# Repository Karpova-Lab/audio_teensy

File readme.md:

# Teensy Audio Board for pyControl

This device connects with a [pyControl breakout](https://karpova-lab.github.io/pyControl-D-Series-Breakout/index.html) to play audio tones. 
A [Teensy 3.2](https://www.pjrc.com/teensy/index.html) generates an i2s audio signal which is later decompressed and amplified by the SGTL5000 codec IC. 
A left and right amplified signal is output to two separate mono headphone jacks. The design of this pcb is based on the [Teensy Audio Adaptor Board](https://www.pjrc.com/store/teensy3_audio.html).

## Bill Of Materials
| Qty | Reference  | Description         | Value/MPN                                                                                                            | 
|-----|------------|---------------------|----------------------------------------------------------------------------------------------------------------------|
| 3   | C2, C3, C7 | 0603 Capacitor      | [100nF](https://www.digikey.com/products/en?keywords=1276-1258-1-ND)                                                 | 
| 1   | C4         | 0603 Capacitor      | [150nF](https://www.digikey.com/product-detail/en/kemet/C0603C154K8RACTU/399-7862-1-ND/3471585)                      | 
| 2   | C5, C1     | 0603 Capacitor      | [1.0µF](https://www.digikey.com/products/en?keywords=1276-6524-1-ND)                                                 | 
| 1   | C6         | 0603 Capacitor      | [2.2µF](https://www.digikey.com/products/en?keywords=1276-1040-1-ND)                                                 | 
| 1   | FB1        | 0603 Ferrite Bead   | [600Ω @ 100MHz](https://www.digikey.com/products/en?keywords=445-2166-1-ND)                                          | 
| 1   | J1         | RJ45 Jack           | [54602-908LF](https://www.digikey.com/en/products/detail/54602-908LF/609-1046-ND/1001360)                            | 
| 2   | J3, J2     | 14pin Female Header | [SSM-114-L-SV-BE](https://www.digikey.com/products/en?keywords=SSM-114-L-SV-BE-ND)                                   | 
| 2   | J4, J5     | Mono Audio Jack     | [4832.2230](https://www.digikey.com/en/products/detail/schurter-inc/4832-2230/1731054?s=N4IgTCBcDaICwA4BsBaAzHAjAdhAXQF8g)| 
| 1   | R1         | 0603 Resistor       | [100Ω](https://www.digikey.com/products/en?keywords=311-100HRCT-ND)                                                  | 
| 2   | R3, R2     | 0603 Resistor       | [2.2KΩ](https://www.digikey.com/products/en?keywords=A130093CT-ND)                                                   | 
| 1   | U2         | 1.8V LDO Regulator  | [AP7313](https://www.digikey.com/product-detail/en/diodes-incorporated/AP7313-18SAG-7/AP7313-18SAG-7DICT-ND/2270838) | 
| 1   | U3         | Codec IC            | [SGTL5000](https://www.digikey.com/products/en?keywords=SGTL5000XNAA3R2CT-ND)                                        | 

### [View interactive BOM](https://karpova-lab.github.io/audio_teensy/ibom)

## Example Firmware for Teensy
This following firmware creates 6.5KHz and 14KHz sine waves that are frequency modulated at 6.66 Hz. 
It responds to commands received over serial UART. 'L' plays the left tone, 'R' plays the right tone, 'S' stops playing both tones, 'V,5' adjust the volume to 5. 
This firmware is loaded onto the Teensy microcontroller. 

[Audio System Design Tool](https://www.pjrc.com/teensy/gui/index.html)

```c++
#include <Audio.h>
#include <Wire.h>
#include <SPI.h>
#include <SD.h>
#include <SerialFlash.h>

// GUItool: begin automatically generated code
AudioSynthWaveformSine   modulation;     //xy=323.0056381225586,328.0056438446045
AudioSynthWaveformModulated left_tone;   //xy=530.0056648254395,308.0056457519531
AudioSynthWaveformModulated right_tone;   //xy=533.1874694824219,363.0965919494629
AudioMixer4              mixer;         //xy=719.1874771118164,330.0965805053711
AudioOutputI2S           i2s;            //xy=868.0056648254395,332.0056505203247
AudioConnection          patchCord1(modulation, 0, left_tone, 0);
AudioConnection          patchCord2(modulation, 0, right_tone, 0);
AudioConnection          patchCord3(left_tone, 0, mixer, 0);
AudioConnection          patchCord4(right_tone, 0, mixer, 1);
AudioConnection          patchCord5(mixer, 0, i2s, 0);
AudioConnection          patchCord6(mixer, 0, i2s, 1);
AudioControlSGTL5000     codec;          //xy=607.0056762695312,492.0056781768799
// GUItool: end automatically generated code

int current_waveform=0;
const int LED = 13;

void setup() {
  // put your setup code here, to run once:
  AudioMemory(10);
  codec.enable();
  codec.volume(0.10);

  modulation.frequency(20/3.0);
  modulation.amplitude(.019);

  left_tone.frequency(6500);
  left_tone.amplitude(1.0);
  right_tone.frequency(14000);
  right_tone.amplitude(1.0);

  mixer.gain(0,0);
  mixer.gain(1,0);

  current_waveform = WAVEFORM_SINE;
  left_tone.begin(current_waveform);
  right_tone.begin(current_waveform);
  Serial1.begin(9600);
  pinMode(LED,OUTPUT);
  digitalWrite(LED,LOW);
 }

void loop() {
  if (Serial1.available()){
    char msg = Serial1.read();
    if (msg=='L' | msg == 'R' | msg == 'S' | msg == 'V'){
      if (msg=='L'){ // left tone
        mixer.gain(0,1);
        mixer.gain(1,0);
        digitalWrite(LED,HIGH);
      }
      else if (msg=='R'){ //right tone
        mixer.gain(0,0);
        mixer.gain(1,1);
        digitalWrite(LED,HIGH);
      }
      else if (msg=='S'){ 
        mixer.gain(0,0);
        mixer.gain(1,0);
        digitalWrite(LED,LOW);
      }
      else if (msg=='V'){ 
        float volume = parseData();
        volume = 2*volume/100.0;
        codec.volume(volume);
      }
    }    
  }
}

int parseData(){
  char msgData[10] = "";
  Serial1.readBytesUntil('\n',msgData,10);
  char* msgPointer;
  msgPointer = strtok(msgData,",");
  return atoi(msgPointer);
}
```

## pyControl Device file

``` python
from machine import UART
from array import array

class Teensy_audio():
    def __init__(self, port):
        assert port.UART is not None, '! Teensy Audio Player needs a port with UART.'
        self.uart = UART(port.UART, 9600)
        self.uart.init(9600, bits=8, parity=None, stop=1, timeout=1)
        self.uart.write('S')

    def play(self, side):
        if side == 'Left':
            self.uart.write('L')
        elif side == 'Right':
            self.uart.write('R')
        return True

    def stop(self):
        self.uart.write('S')
        return False

    def set_volume(self, volume): # Between 1 - 65
        self.uart.write('V,{}'.format(volume))
```

## Latency
The start and stop latencies are both about 6.5 ± 1 ms

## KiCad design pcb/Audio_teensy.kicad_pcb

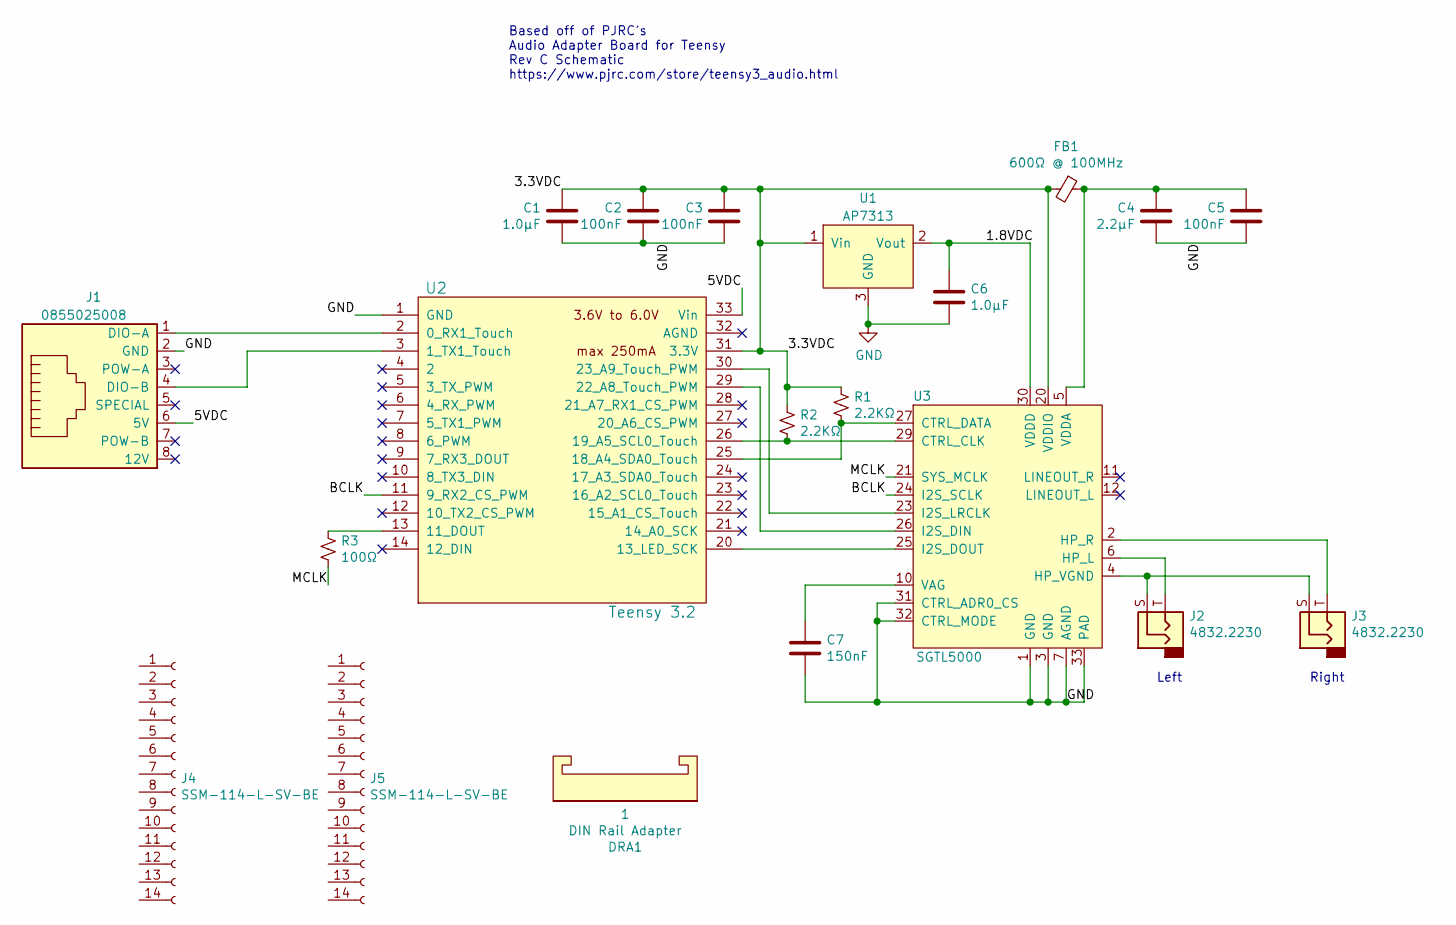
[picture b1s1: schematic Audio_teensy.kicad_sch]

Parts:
C1, C6: 1.0µF; C_0603_1608Metric
C2, C3, C5: 100nF; C_0603_1608Metric
C4: 2.2µF; C_0603_1608Metric
C7: 150nF; C_0603_1608Metric
DRA1: DIN Rail Adapter; DIN_Clip
FB1: 600Ω @ 100MHz; C_0603_1608Metric
J1: 0855025008; RJ45_THP_Vertical
J2, J3: 4832.2230; mono_jack_throughhole
J4, J5: SSM-114-L-SV-BE; PinHeader_1x14_P2.54mm_Vertical_SMD_Pin1Left
R1, R2: 2.2KΩ; R_0603_1608Metric
R3: 100Ω; R_0603_1608Metric
U1: AP7313; TSOT-23
U2: Teensy 3.2; Teensy30_31_32_LC_SMD
U3: SGTL5000; QFN-32-1EP_5x5mm_P0.5mm_EP3.1x3.1mm

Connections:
/1.8VDC: C6.1, U1.2 (Vout), U3.30 (VDDD)
/3.3VDC: C1.2, C2.2, C3.2, FB1.2, R1.1, R2.1, U1.1 (Vin), U2.31 (3.3V), U3.20 (VDDIO)
/5VDC: J1.6 (5V), U2.33 (Vin)
/BCLK: U2.11 (9_RX2_CS_PWM), U3.24 (I2S_SCLK)
/MCLK: R3.2, U3.21 (SYS_MCLK)
GND: C1.1, C2.1, C3.1, C4.1, C5.1, C6.2, C7.2, J1.2 (GND), U1.3 (GND), U2.1 (GND), U3.1 (GND), U3.3 (GND), U3.7 (AGND), U3.31 (CTRL_ADR0_CS), U3.32 (CTRL_MODE), U3.33 (PAD)
unnamed: C4.2, C5.2, FB1.1, U3.5 (VDDA)
unnamed: C7.1, U3.10 (VAG)
unnamed: J1.1 (DIO-A), U2.2 (0_RX1_Touch)
unnamed: J1.4 (DIO-B), U2.3 (1_TX1_Touch)
unnamed: J2.S, J3.S, U3.4 (HP_VGND)
unnamed: J2.T, U3.6 (HP_L)
unnamed: J3.T, U3.2 (HP_R)
unnamed: R1.2, U2.25 (18_A4_SDA0_Touch), U3.27 (CTRL_DATA)
unnamed: R2.2, U2.26 (19_A5_SCL0_Touch), U3.29 (CTRL_CLK)
unnamed: R3.1, U2.13 (11_DOUT)
unnamed: U2.20 (13_LED_SCK), U3.25 (I2S_DOUT)
unnamed: U2.29 (22_A8_Touch_PWM), U3.26 (I2S_DIN)
unnamed: U2.30 (23_A9_Touch_PWM), U3.23 (I2S_LRCLK)

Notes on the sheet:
Based off of PJRC’s Audio Adapter Board for Teensy Rev C Schematic https://www.pjrc.com/store/teensy3_audio.html
Left
Right

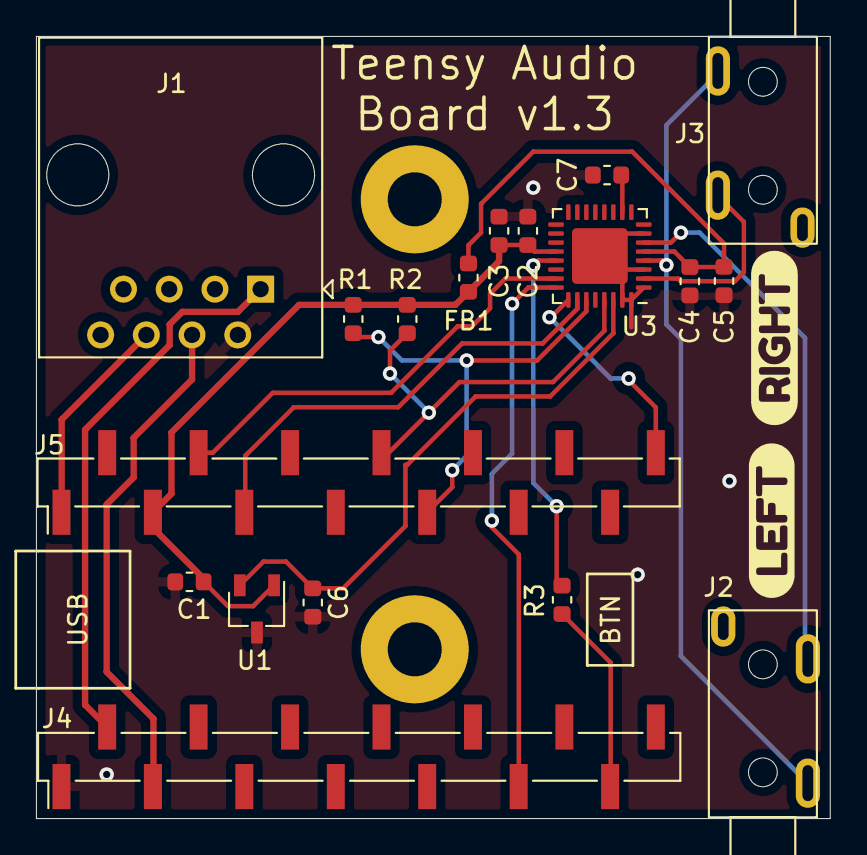
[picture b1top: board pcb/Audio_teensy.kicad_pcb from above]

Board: 2 copper layers, 44.1 x 43.5 mm, 22 parts (0 on the bottom side), 19 nets.

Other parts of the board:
svg2mod, svg2mod#2: G***; svg2mod

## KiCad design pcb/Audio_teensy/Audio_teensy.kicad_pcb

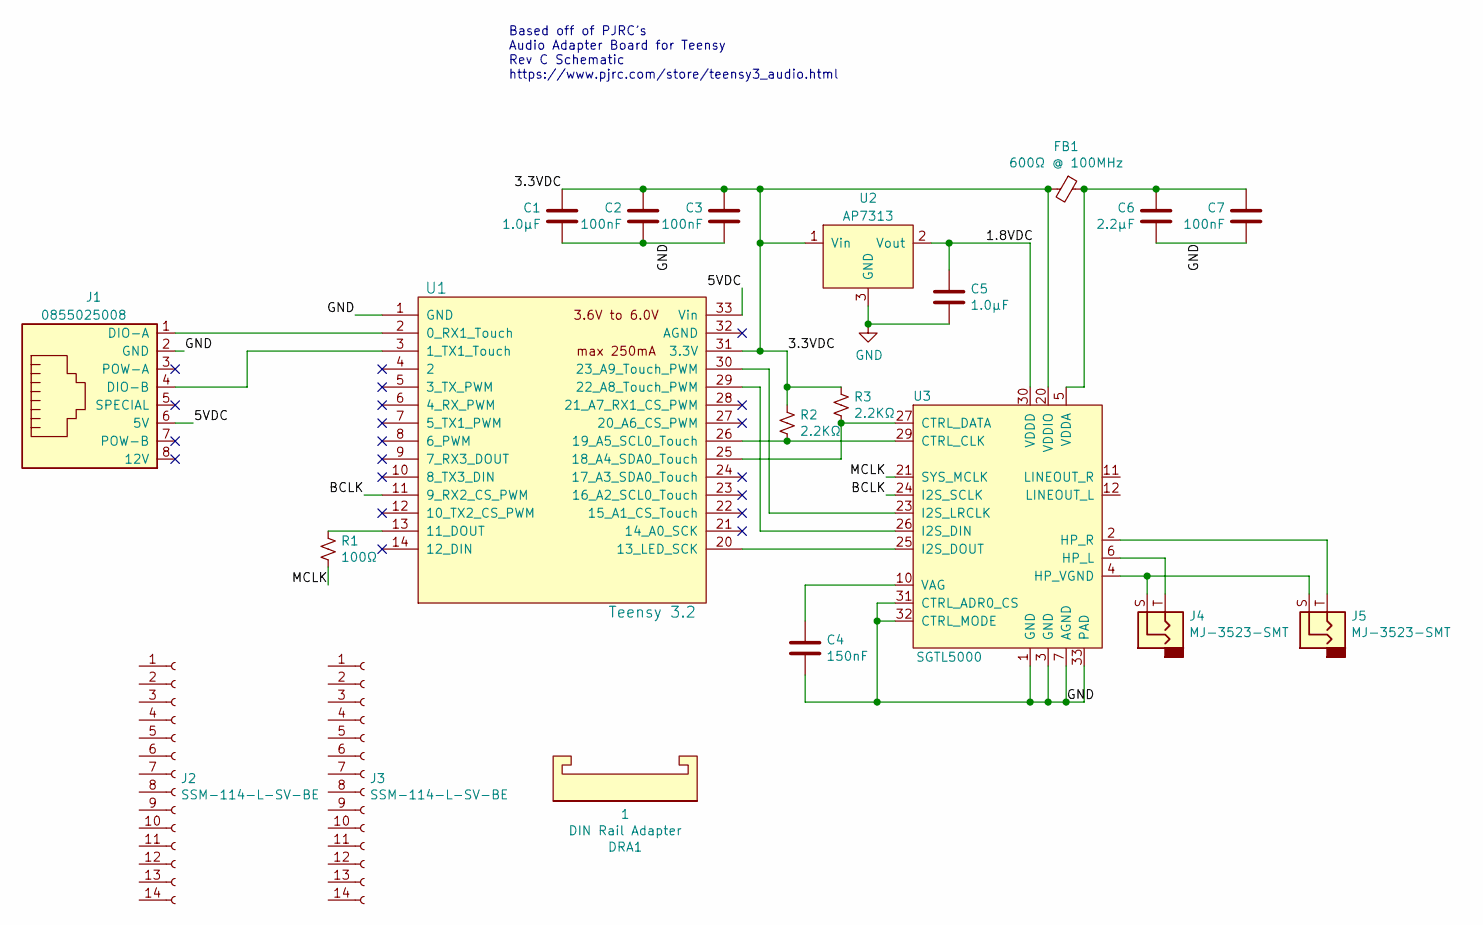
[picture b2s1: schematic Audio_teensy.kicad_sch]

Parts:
C1, C5: 1.0µF; C_0603_1608Metric
C2, C3, C7: 100nF; C_0603_1608Metric
C4: 150nF; C_0603_1608Metric
C6: 2.2µF; C_0603_1608Metric
DRA1: DIN Rail Adapter; DIN_Clip
FB1: 600Ω @ 100MHz; C_0603_1608Metric
J1: 0855025008; RJ45_SMD
J2, J3: SSM-114-L-SV-BE; PinHeader_1x14_P2.54mm_Vertical_SMD_Pin1Left
J4, J5: MJ-3523-SMT; MonoJack
R1: 100Ω; R_0603_1608Metric
R2, R3: 2.2KΩ; R_0603_1608Metric
U1: Teensy 3.2; Teensy30_31_32_LC_SMD
U2: AP7313; TSOT-23
U3: SGTL5000; QFN-32-1EP_5x5mm_P0.5mm_EP3.1x3.1mm

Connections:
/1.8VDC: C5.1, U2.2 (Vout), U3.30 (VDDD)
/3.3VDC: C1.2, C2.2, C3.2, FB1.2, R2.1, R3.1, U1.31 (3.3V), U2.1 (Vin), U3.20 (VDDIO)
/5VDC: J1.6 (5V), U1.33 (Vin)
/BCLK: U1.11 (9_RX2_CS_PWM), U3.24 (I2S_SCLK)
/MCLK: R1.2, U3.21 (SYS_MCLK)
GND: C1.1, C2.1, C3.1, C4.2, C5.2, C6.1, C7.1, J1.2 (GND), U1.1 (GND), U2.3 (GND), U3.1 (GND), U3.3 (GND), U3.7 (AGND), U3.31 (CTRL_ADR0_CS), U3.32 (CTRL_MODE), U3.33 (PAD)
unnamed: C4.1, U3.10 (VAG)
unnamed: C6.2, C7.2, FB1.1, U3.5 (VDDA)
unnamed: J1.1 (DIO-A), U1.2 (0_RX1_Touch)
unnamed: J1.4 (DIO-B), U1.3 (1_TX1_Touch)
unnamed: J4.S, J5.S, U3.4 (HP_VGND)
unnamed: J4.T, U3.6 (HP_L)
unnamed: J5.T, U3.2 (HP_R)
unnamed: R1.1, U1.13 (11_DOUT)
unnamed: R2.2, U1.26 (19_A5_SCL0_Touch), U3.29 (CTRL_CLK)
unnamed: R3.2, U1.25 (18_A4_SDA0_Touch), U3.27 (CTRL_DATA)
unnamed: U1.20 (13_LED_SCK), U3.25 (I2S_DOUT)
unnamed: U1.29 (22_A8_Touch_PWM), U3.26 (I2S_DIN)
unnamed: U1.30 (23_A9_Touch_PWM), U3.23 (I2S_LRCLK)

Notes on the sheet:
Based off of PJRC’s Audio Adapter Board for Teensy Rev C Schematic https://www.pjrc.com/store/teensy3_audio.html

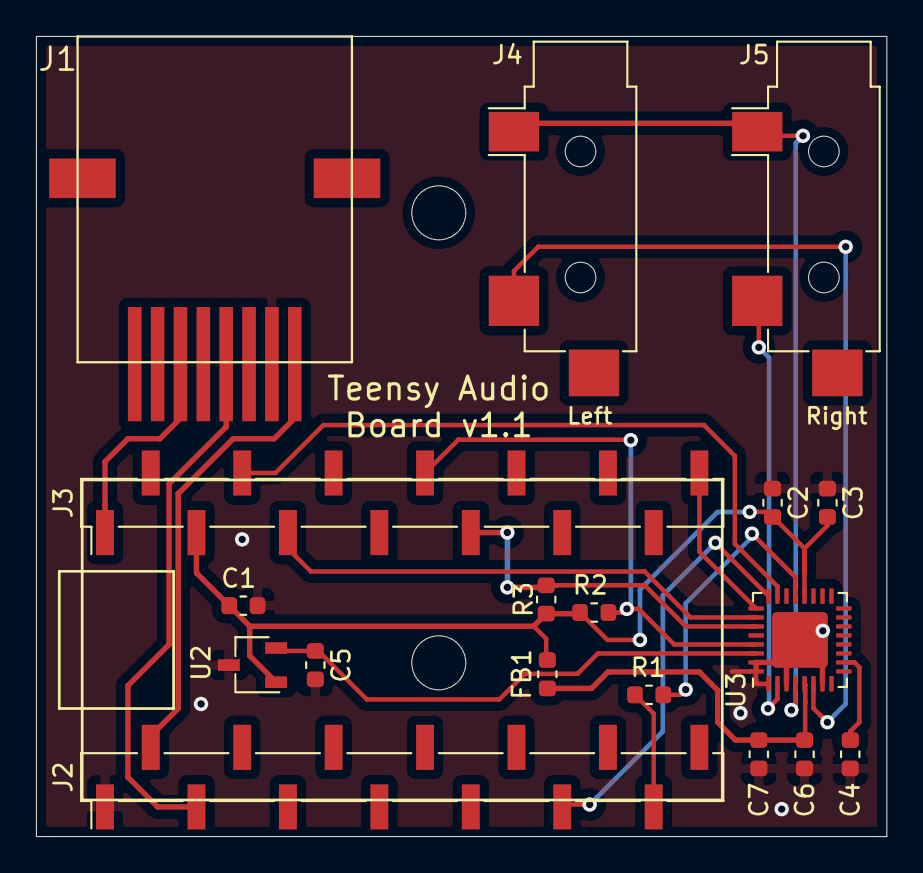
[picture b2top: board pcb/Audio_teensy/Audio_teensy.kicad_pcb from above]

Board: 2 copper layers, 47.2 x 44.5 mm, 20 parts (0 on the bottom side), 19 nets.

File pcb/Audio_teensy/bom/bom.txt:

"Qty","Reference","Description","Value/MPN","Purchase Link"
"3","C2, C3, C7","0603 Capacitor","100nF","https://www.digikey.com/products/en?keywords=1276-1258-1-ND"
"1","C4","0603 Capacitor","150nF","https://www.digikey.com/product-detail/en/kemet/C0603C154K8R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"
"2","C5, C1","0603 Capacitor","1.0µF","https://www.digikey.com/products/en?keywords=1276-6524-1-ND"
"1","C6","0603 Capacitor","2.2µF","https://www.digikey.com/products/en?keywords=1276-1040-1-ND"
"1","FB1","0603 Ferrite Bead","600Ω @ 100MHz","https://www.digikey.com/products/en?keywords=445-2166-1-ND"
"1","J1","RJ45 Jack","0855025008","https://www.digikey.com/products/en?keywords=WM3547CT-ND"
"2","J3, J2","14pin Female Header","SSM-114-L-SV-BE","https://www.digikey.com/products/en?keywords=SSM-114-L-SV-BE-ND"
"2","J4, J5","Mono Audio Jack","MJ-3523-SMT","https://www.digikey.com/products/en?keywords=CP-3523MJCT-ND"
"1","R1","0603 Resistor","100Ω","https://www.digikey.com/products/en?keywords=311-100HRCT-ND"
"2","R3, R2","0603 Resistor","2.2KΩ","https://www.digikey.com/products/en?keywords=A130093CT-ND"
"1","U2","1.8V LDO Regulator","AP7313","https://www.digikey.com/product-detail/en/diodes-incorporate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"
"1","U3","Codec IC","SGTL5000","https://www.digikey.com/products/en?keywords=SGTL5000XNAA3R2CT-ND"

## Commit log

2019-10-30 added teensy to library
2019-10-30 added SGTL500 audio codec ic to library
2019-11-01 v1.0
2019-11-02 working prototype
2019-11-08 v1.1 AP3713 regulator pins were mapped incorrectly to footprint. Swapped Vin and GND. Added descriptions and purchase links for all components.
2019-11-14 Adjusted modulation wave. LED now indicates whether tone is being played.
2019-11-15 renamed teensy firmware
2019-11-15 updated readme. cleaned up teensy code
2019-11-18 Interactive BOM is now hosted on github pages. Added link in readme pointing to it.
2019-11-18 Now building github page from docs folder
2019-12-11 Added licenses to readme
2020-08-31 Added Audio Library. Added bloop to available sounds
2021-09-01 readme update
2021-09-01 picture for readme
2021-09-01 upgrade to kicad 5.99
2021-09-01 moved kicad files up into PCB folder
2021-09-02 changed to through hole components
    rearranged mono jacks to point towards opposite sides
2021-10-13 pcb v1.3
2022-11-22 BOM update to reflect changes in PCB v1.3
